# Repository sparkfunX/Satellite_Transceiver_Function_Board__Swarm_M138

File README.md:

SparkX Satellite Transceiver Function Board - Swarm M138
========================================

<p align="center">

</p>

*[SparkX Satellite Transceiver Function Board - Swarm M138 (SPX-20107)](https://www.sparkfun.com/products/20107)*

The [SparkX Satellite Transceiver Function Board - Swarm M138 (SPX-20107)](https://www.sparkfun.com/products/20107) is an adapter which allows you to add Swarm Satellite connectivity
to your [MicroMod](https://www.sparkfun.com/micromod) project. It is designed to be plugged into the [MicroMod Main Board - Single](https://www.sparkfun.com/products/18575)
or [MicroMod Main Board - Double](https://www.sparkfun.com/products/18575). You can then install the Swarm M138 satellite modem and communicate using our dedicated 
[Swarm Satellite Arduino Library](https://github.com/sparkfun/SparkFun_Swarm_Satellite_Arduino_Library).

**Please note: the Swarm M138 modem is not included with the function board.** You will need to purchase the [Satellite Transceiver Breakout - Swarm M138 (SPX-19236)](https://www.sparkfun.com/products/19236)
separately to obtain the modem, antenna and ground plane.

Repository Contents
-------------------

* **[/docs](/docs/)** - Online documentation files
    * [board_files](/docs/board_files/) - Files for the product design
        * [Eagle design files](/docs/board_files/Satellite_Transceiver_Function_Board__Swarm_M138_x04.zip) (.zip)
        * [Schematic](/docs/board_files/Schematic.pdf) (.pdf)
        * [Dimensions](/docs/board_files/Dimensions.png) (.png)
    * [img/hookup_guide/](/docs/img/hookup_guide/) - Images for hookup guide documentation
* **[/Hardware](/Hardware/)** - Eagle design files (.brd, .sch)

Documentation
--------------
* **[Hookup Guide (mkdocs)](https://sparkfunx.github.io/Satellite_Transceiver_Function_Board__Swarm_M138/)** - Hookup guide for the SparkX Satellite Transceiver Function Board - Swarm M138 hosted by GitHub pages.

Product Versions
----------------
* [SPX-20107](https://www.sparkfun.com/products/20107) - Initial SparkX Release

License Information
-------------------

This product is _**open source**_! 

Please review the LICENSE.md file for license information. 

If you have any questions or concerns on licensing, please contact technical support on our [SparkFun forums](https://forum.sparkfun.com/viewforum.php?f=152).

Distributed as-is; no warranty is given.

- Your friends at SparkFun.

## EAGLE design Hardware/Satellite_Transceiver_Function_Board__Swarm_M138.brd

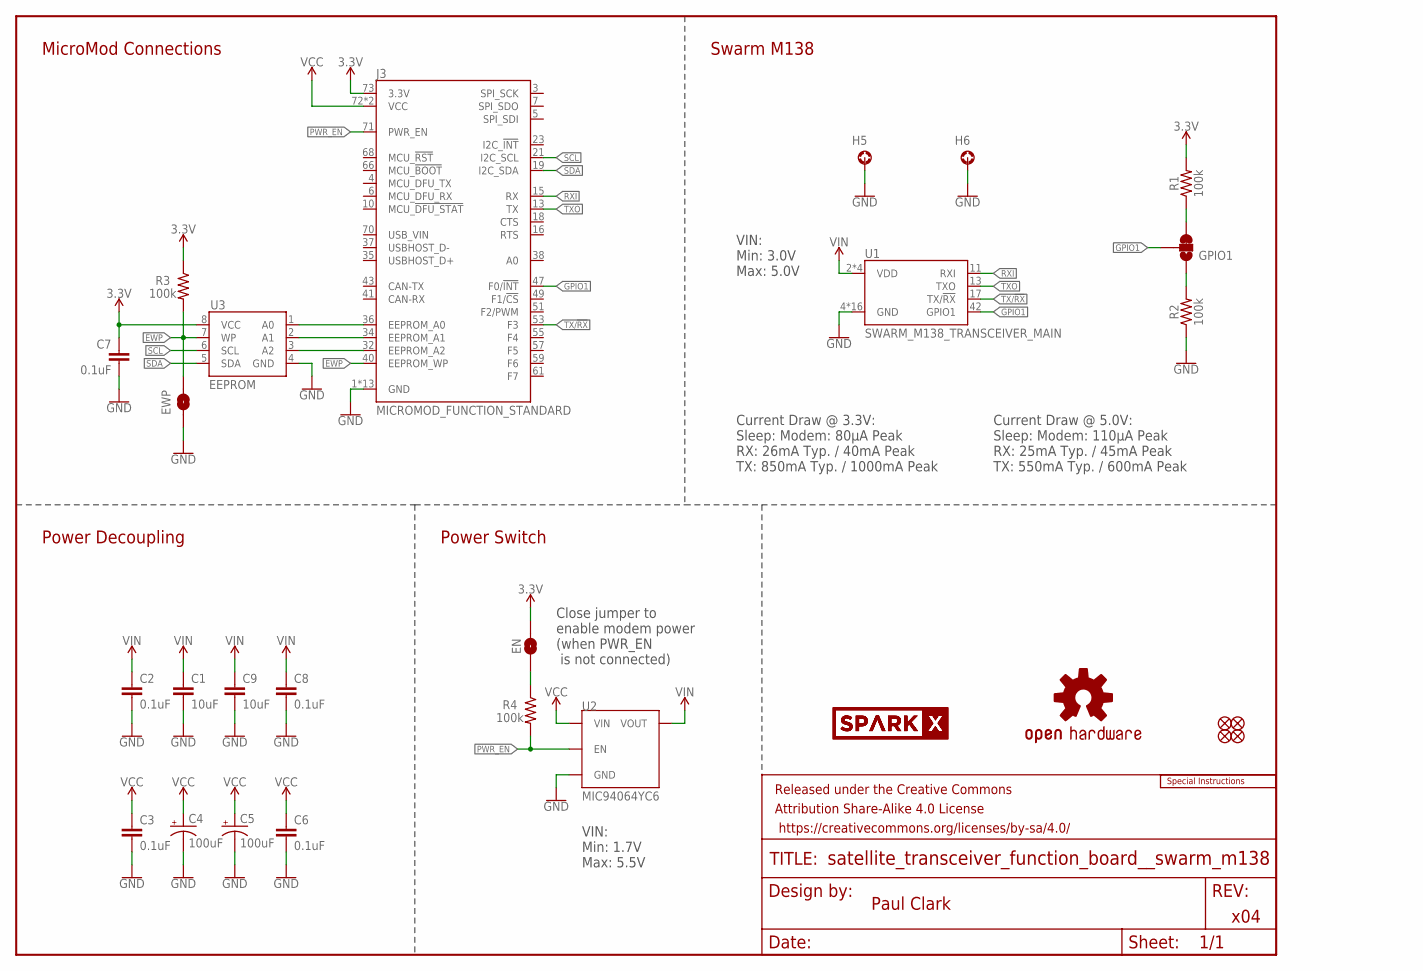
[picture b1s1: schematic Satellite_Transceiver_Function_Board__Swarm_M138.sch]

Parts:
C1, C9: 10uF; 0603
C2, C3, C6, C7, C8: 0.1uF; 0603
C4, C5: 100uF; EIA3528
EN: JUMPER-SMT_2_NO_SILK; SMT-JUMPER_2_NO_SILK
EWP: JUMPER-SMT_2_NO_SILK; SMT-JUMPER_2_NO_SILK
FD1, FD2, FD3, FD4: FIDUCIAL1X2; FIDUCIAL-1X2
FRAME1: FRAME-LETTER; CREATIVE_COMMONS
GPIO1: JUMPER-SMT_3_1-NC_TRACE_SILK; SMT-JUMPER_3_1-NC_TRACE_SILK
H5, H6: STAND-OFF-REFLOW-M2.5_1.5MM_TALL; STAND-OFF-REFLOW-M2.5
J3: MICROMOD_FUNCTION_STANDARD; M.2-CARD-E-22_FUNCTION_STANDARD
LOGO1: SPECIAL_INSTRUCTIONS-ORDERING; ORDERING_INSTRUCTIONS
LOGO2: OSHW-LOGOS; OSHW-LOGO-S
R1, R2, R3, R4: 100k; 0603
U1: SWARM_M138_TRANSCEIVER_MAIN; M.2-SWARM-M138-A
U2: MIC94064YC6; SC-70-6
U3: EEPROM; SO08
U$1, U$2: SPARKX-LOGO5; SPARKX-LARGE

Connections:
3.3V: C7.1, EN.2, J3.73 (3.3V), R1.2, R3.1, U3.8 (VCC)
A0: J3.36 (EEPROM_A0), U3.1 (A0)
A1: J3.34 (EEPROM_A1), U3.2 (A1)
A2: J3.32 (EEPROM_A2), U3.3 (A2)
EWP: EWP.2, J3.40 (EEPROM_WP), R3.2, U3.7 (WP)
GND: C1.2, C2.2, C3.2, C4.C (-), C5.C (-), C6.2, C7.2, C8.2, C9.2, EWP.1, H5.1, H6.1, J3.1 (GND), J3.2 (GND), J3.8 (GND), J3.33 (GND), J3.39 (GND), J3.45 (GND), J3.75 (GND), J3.GND1 (GND), J3.GND2 (GND), J3.GND3 (GND), J3.GND4 (GND), J3.GND5 (GND), J3.GND6 (GND), R2.1, U1.4 (GND), U1.9 (GND), U1.15 (GND), U1.18 (GND), U1.21 (GND), U1.26 (GND), U1.27 (GND), U1.29 (GND), U1.34 (GND), U1.35 (GND), U1.37 (GND), U1.40 (GND), U1.43 (GND), U1.50 (GND), U1.A1 (GND), U1.A2 (GND), U2.2 (GND), U2.5 (GND), U3.4 (GND)
GPIO1: GPIO1.2, J3.47 (F0/!INT!), U1.42 (GPIO1)
unnamed: EN.1, R4.1
unnamed: GPIO1.3, R1.1
unnamed: GPIO1.1, R2.2
PWR_EN: J3.71 (PWR_EN), R4.2, U2.3 (EN)
RXI: J3.15 (RX), U1.11 (RXI)
SCL: J3.21 (I2C_SCL), U3.6 (SCL)
SDA: J3.19 (I2C_SDA), U3.5 (SDA)
TX/!RX!: J3.53 (F3), U1.17 (TX/!RX!)
TXO: J3.13 (TX), U1.13 (TXO)
VCC: C3.1, C4.A (+), C5.A (+), C6.1, J3.72 (VCC), J3.74 (VCC), U2.4 (VIN)
VIN: C1.1, C2.1, C8.1, C9.1, U1.2 (VDD), U1.39 (VDD), U1.41 (VDD), U1.52 (VDD), U2.1 (VOUT)

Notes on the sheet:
x04
Paul Clark
Power Switch
Power Decoupling
Swarm M138
VIN: Min: 3.0V Max: 5.0V
Current Draw @ 3.3V: Sleep: Modem: 80µA Peak RX: 26mA Typ. / 40mA Peak TX: 850mA Typ. / 1000mA Peak
Current Draw @ 5.0V: Sleep: Modem: 110µA Peak RX: 25mA Typ. / 45mA Peak TX: 550mA Typ. / 600mA Peak
MicroMod Connections
VIN: Min: 1.7V Max: 5.5V
Close jumper to enable modem power (when PWR_EN is not connected)

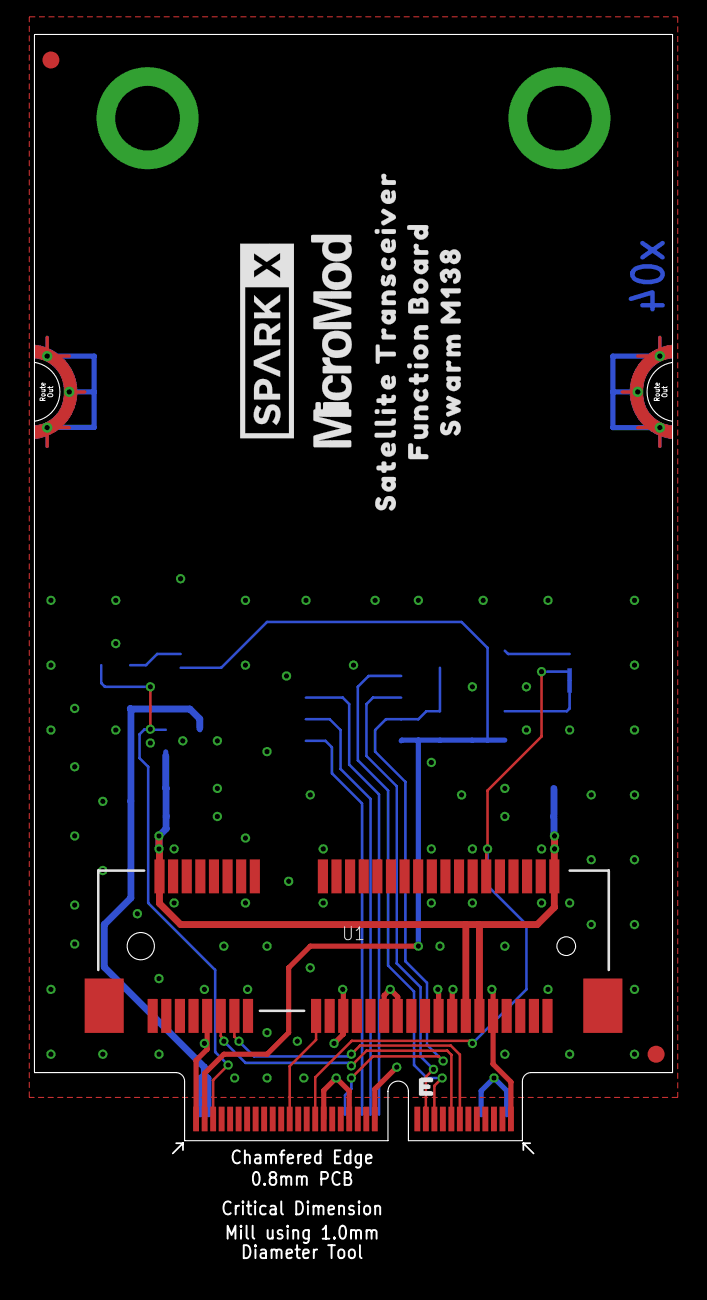
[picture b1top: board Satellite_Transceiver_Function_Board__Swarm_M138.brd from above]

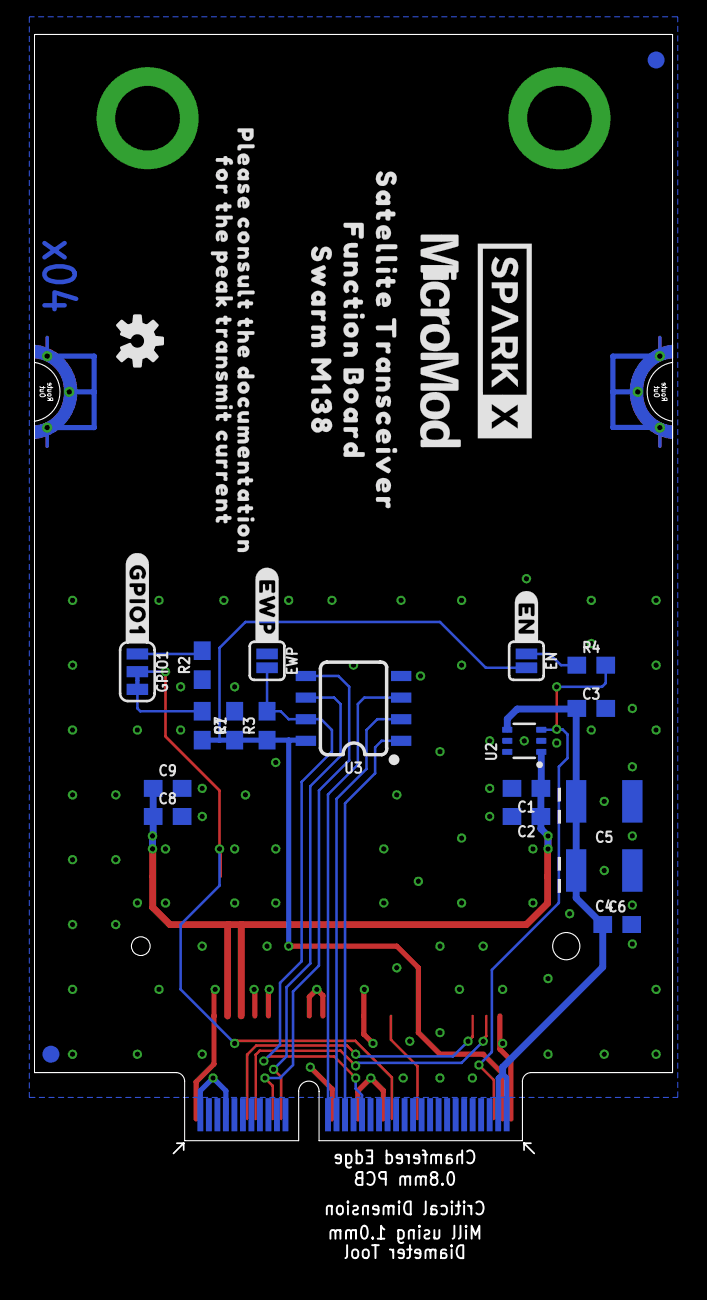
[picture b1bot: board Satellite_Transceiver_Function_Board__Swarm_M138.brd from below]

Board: 2 copper layers, 37.4 x 72.3 mm, 44 parts (31 on the bottom side), 18 nets.

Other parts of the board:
U$3, U$7: FUNCTION_BOARD0
U$4, U$5: SATELLITE_TRANSCEIVER0
U$6: PLEASE_CONSULT_THE_DOCUMENTATION0
U$8: #EWP#0
U$9, U$10: MICROMOD_LOGO_.5
U$11: #EN#0
U$19: #GPIO1#0
U$31: FOR_THE_PEAK_TRANSMIT_CURRENT1
U$40, U$41: SWARM_M1381

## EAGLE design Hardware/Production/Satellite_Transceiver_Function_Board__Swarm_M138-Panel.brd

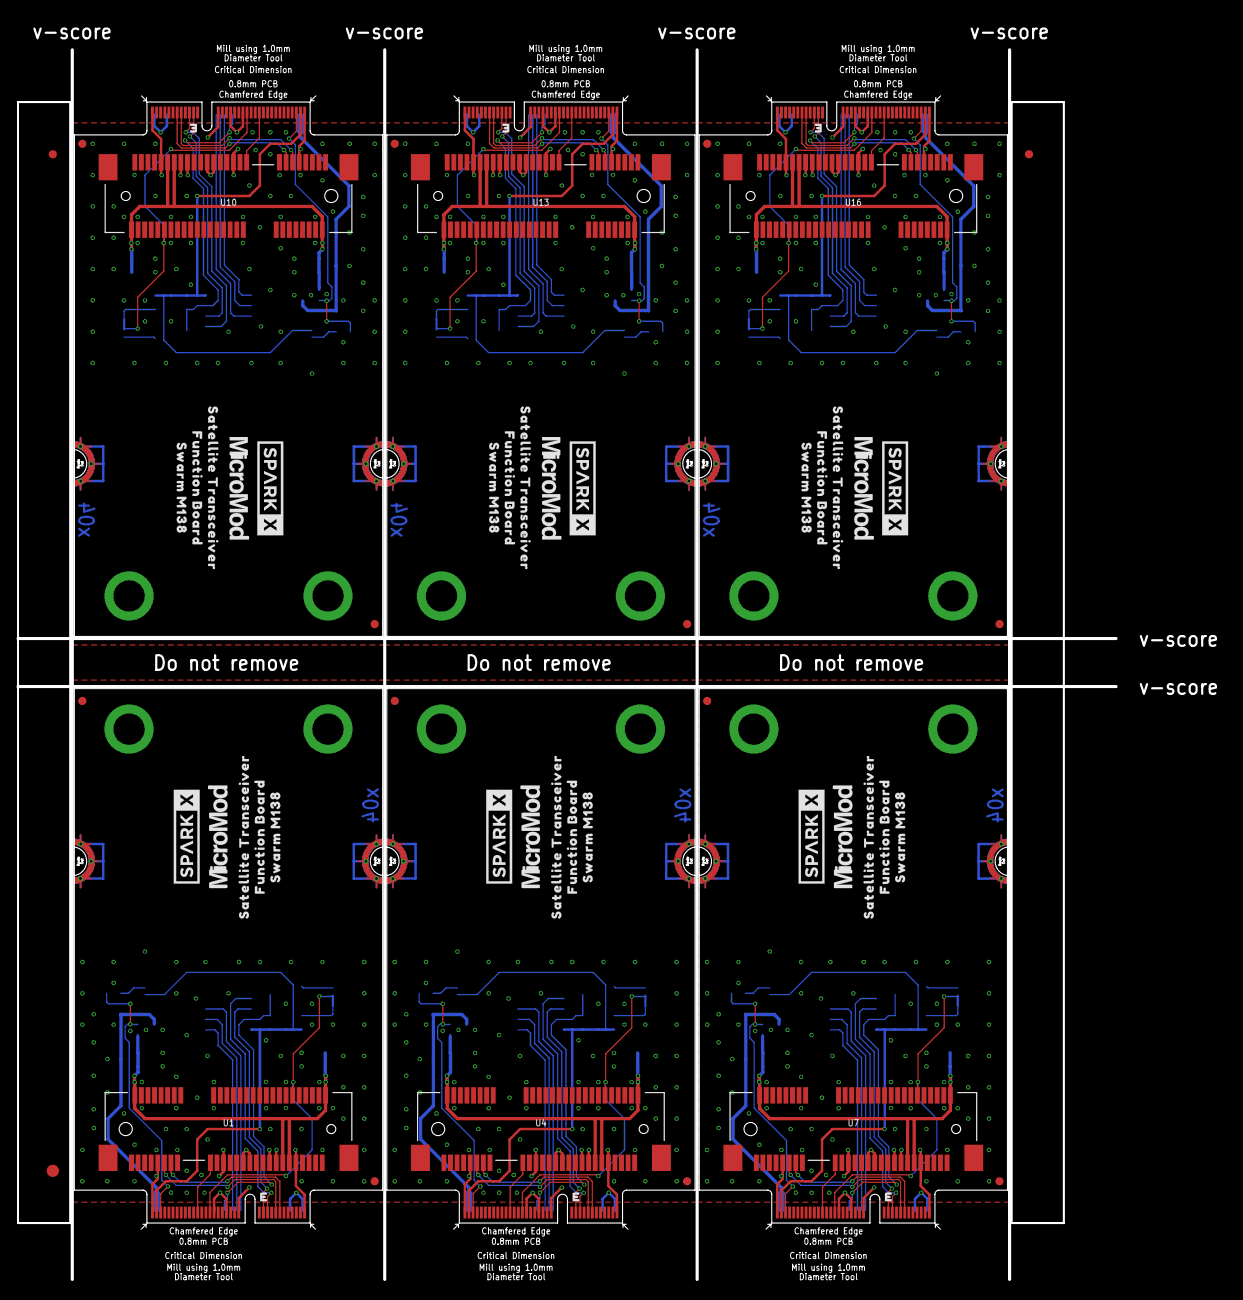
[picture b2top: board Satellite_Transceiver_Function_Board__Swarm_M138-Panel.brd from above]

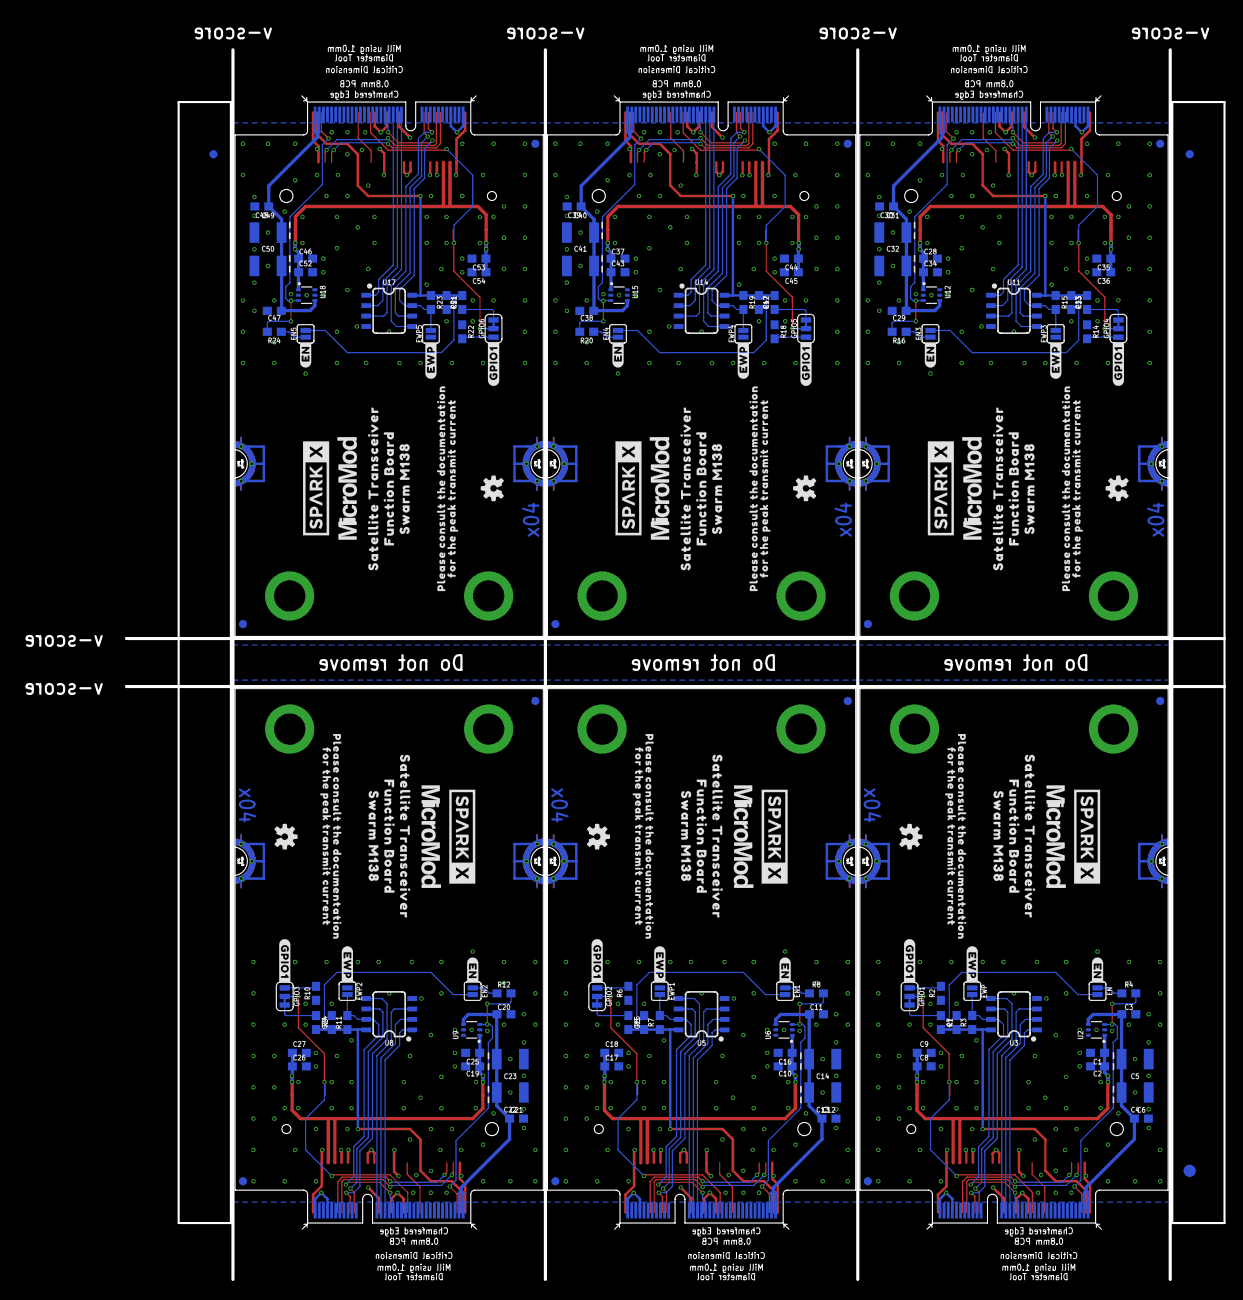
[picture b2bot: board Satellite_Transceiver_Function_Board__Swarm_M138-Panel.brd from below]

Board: 2 copper layers, 146.7 x 153.7 mm, 258 parts (189 on the bottom side), 108 nets.

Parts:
C1, C9, C16, C18, C25, C27, C34, C36, C43, C45, C52, C54: 10uF; 0603
C2, C3, C6, C7, C8, C10, C11, C12, C15, C17, C19, C20, C21, C24, C26, C28, C29, C30, C33, C35, C37, C38, C39, C42, C44, C46, C47, C48, C51, C53: 0.1uF; 0603
C4, C5, C13, C14, C22, C23, C31, C32, C40, C41, C49, C50: 100uF; EIA3528
E$1, E$2, E$3, E$4: FIDUCIAL-1X2
E$5, E$6: FIDUCIAL-1.5X3
EN, EN1, EN2, EN3, EN4, EN5: JUMPER-SMT_2_NO_SILK; SMT-JUMPER_2_NO_SILK
EWP, EWP1, EWP2, EWP3, EWP4, EWP5: JUMPER-SMT_2_NO_SILK; SMT-JUMPER_2_NO_SILK
FD1, FD2, FD3, FD4, FD5, FD6, FD7, FD8, FD9, FD10, FD11, FD12, FD13, FD14, FD15, FD16, FD17, FD18, FD19, FD20, FD21, FD22, FD23, FD24: FIDUCIAL1X2; FIDUCIAL-1X2
GPIO1, GPIO2, GPIO3, GPIO4, GPIO5, GPIO6: JUMPER-SMT_3_1-NC_TRACE_SILK; SMT-JUMPER_3_1-NC_TRACE_SILK
H1, H2, H3, H4, H5, H6, H7, H8, H9, H10, H11, H12: STAND-OFF-REFLOW-M2.5_1.5MM_TALL; STAND-OFF-REFLOW-M2.5
J1, J2, J3, J4, J5, J6: MICROMOD_FUNCTION_STANDARD; M.2-CARD-E-22_FUNCTION_STANDARD
LOGO1, LOGO2, LOGO3, LOGO4, LOGO5, LOGO6: OSHW-LOGOS; OSHW-LOGO-S
R1, R2, R3, R4, R5, R6, R7, R8, R9, R10, R11, R12, R13, R14, R15, R16, R17, R18, R19, R20, R21, R22, R23, R24: 100k; 0603
U1, U4, U7, U10, U13, U16: SWARM_M138_TRANSCEIVER_MAIN; M.2-SWARM-M138-A
U2, U6, U9, U12, U15, U18: MIC94064YC6; SC-70-6
U3, U5, U8, U11, U14, U17: EEPROM; SO08
U$1, U$2, U$12, U$13, U$28, U$29, U$46, U$47, U$61, U$62, U$76, U$77: SPARKX-LOGO5; SPARKX-LARGE
U$3, U$7, U$20, U$23, U$36, U$39, U$53, U$56, U$68, U$71, U$83, U$86: FUNCTION_BOARD0
U$4, U$5, U$21, U$22, U$37, U$38, U$54, U$55, U$69, U$70, U$84, U$85: SATELLITE_TRANSCEIVER0
U$6, U$17, U$34, U$51, U$66, U$81: PLEASE_CONSULT_THE_DOCUMENTATION0
U$8, U$24, U$42, U$57, U$72, U$87: #EWP#0
U$9, U$10, U$25, U$26, U$43, U$44, U$58, U$59, U$73, U$74, U$88, U$89: MICROMOD_LOGO_.5
U$11, U$27, U$45, U$60, U$75, U$90: #EN#0
U$14, U$19, U$30, U$48, U$63, U$78: #GPIO1#0
U$15, U$16, U$32, U$33, U$40, U$41, U$49, U$50, U$64, U$65, U$79, U$80: SWARM_M1381
U$18, U$31, U$35, U$52, U$67, U$82: FOR_THE_PEAK_TRANSMIT_CURRENT1

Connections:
3.3V: C7.1, EN.2, J3.73, R1.2, R3.1, U3.8
3.3V1: C15.1, EN1.2, J1.73, R5.2, R7.1, U5.8
3.3V2: C24.1, EN2.2, J2.73, R9.2, R11.1, U8.8
3.3V3: C33.1, EN3.2, J4.73, R13.2, R15.1, U11.8
3.3V4: C42.1, EN4.2, J5.73, R17.2, R19.1, U14.8
3.3V5: C51.1, EN5.2, J6.73, R21.2, R23.1, U17.8
A0: J3.36, U3.1
A1: J3.34, U3.2
A2: J3.32, U3.3
A3: J1.36, U5.1
A4: J1.32, U5.3
A5: J1.34, U5.2
A6: J2.36, U8.1
A7: J2.32, U8.3
A8: J2.34, U8.2
A9: J4.36, U11.1
A10: J4.32, U11.3
A11: J4.34, U11.2
A12: J5.36, U14.1
A13: J5.32, U14.3
A14: J5.34, U14.2
A15: J6.36, U17.1
A16: J6.32, U17.3
A17: J6.34, U17.2
EWP: EWP.2, J3.40, R3.2, U3.7
EWP1: EWP1.2, J1.40, R7.2, U5.7
EWP2: EWP2.2, J2.40, R11.2, U8.7
EWP3: EWP3.2, J4.40, R15.2, U11.7
EWP4: EWP4.2, J5.40, R19.2, U14.7
EWP5: EWP5.2, J6.40, R23.2, U17.7
GND: C1.2, C2.2, C3.2, C4.C, C5.C, C6.2, C7.2, C8.2, C9.2, EWP.1, H5.1, H6.1, J3.1, J3.2, J3.8, J3.33, J3.39, J3.45, J3.75, J3.GND1, J3.GND2, J3.GND3, J3.GND4, J3.GND5, J3.GND6, R2.1, U1.4, U1.9, U1.15, U1.18, U1.21, U1.26, U1.27, U1.29, U1.34, U1.35, U1.37, U1.40, U1.43, U1.50, U1.A1, U1.A2, U2.2, U2.5, U3.4
GND1: C10.2, C11.2, C12.2, C13.C, C14.C, C15.2, C16.2, C17.2, C18.2, EWP1.1, H1.1, H2.1, J1.1, J1.2, J1.8, J1.33, J1.39, J1.45, J1.75, J1.GND1, J1.GND2, J1.GND3, J1.GND4, J1.GND5, J1.GND6, R6.1, U4.4, U4.9, U4.15, U4.18, U4.21, U4.26, U4.27, U4.29, U4.34, U4.35, U4.37, U4.40, U4.43, U4.50, U4.A1, U4.A2, U5.4, U6.2, U6.5
GND2: C19.2, C20.2, C21.2, C22.C, C23.C, C24.2, C25.2, C26.2, C27.2, EWP2.1, H3.1, H4.1, J2.1, J2.2, J2.8, J2.33, J2.39, J2.45, J2.75, J2.GND1, J2.GND2, J2.GND3, J2.GND4, J2.GND5, J2.GND6, R10.1, U7.4, U7.9, U7.15, U7.18, U7.21, U7.26, U7.27, U7.29, U7.34, U7.35, U7.37, U7.40, U7.43, U7.50, U7.A1, U7.A2, U8.4, U9.2, U9.5
GND3: C28.2, C29.2, C30.2, C31.C, C32.C, C33.2, C34.2, C35.2, C36.2, EWP3.1, H7.1, H8.1, J4.1, J4.2, J4.8, J4.33, J4.39, J4.45, J4.75, J4.GND1, J4.GND2, J4.GND3, J4.GND4, J4.GND5, J4.GND6, R14.1, U10.4, U10.9, U10.15, U10.18, U10.21, U10.26, U10.27, U10.29, U10.34, U10.35, U10.37, U10.40, U10.43, U10.50, U10.A1, U10.A2, U11.4, U12.2, U12.5
GND4: C37.2, C38.2, C39.2, C40.C, C41.C, C42.2, C43.2, C44.2, C45.2, EWP4.1, H9.1, H10.1, J5.1, J5.2, J5.8, J5.33, J5.39, J5.45, J5.75, J5.GND1, J5.GND2, J5.GND3, J5.GND4, J5.GND5, J5.GND6, R18.1, U13.4, U13.9, U13.15, U13.18, U13.21, U13.26, U13.27, U13.29, U13.34, U13.35, U13.37, U13.40, U13.43, U13.50, U13.A1, U13.A2, U14.4, U15.2, U15.5
GND5: C46.2, C47.2, C48.2, C49.C, C50.C, C51.2, C52.2, C53.2, C54.2, EWP5.1, H11.1, H12.1, J6.1, J6.2, J6.8, J6.33, J6.39, J6.45, J6.75, J6.GND1, J6.GND2, J6.GND3, J6.GND4, J6.GND5, J6.GND6, R22.1, U16.4, U16.9, U16.15, U16.18, U16.21, U16.26, U16.27, U16.29, U16.34, U16.35, U16.37, U16.40, U16.43, U16.50, U16.A1, U16.A2, U17.4, U18.2, U18.5
GPIO1: GPIO1.2, J3.47, U1.42
GPIO2: GPIO2.2, J1.47, U4.42
GPIO3: GPIO3.2, J2.47, U7.42
GPIO4: GPIO4.2, J4.47, U10.42
GPIO5: GPIO5.2, J5.47, U13.42
GPIO6: GPIO6.2, J6.47, U16.42
unnamed: EN.1, R4.1
unnamed: GPIO2.3, R5.1
unnamed: GPIO2.1, R6.2
unnamed: EN1.1, R8.1
unnamed: GPIO3.3, R9.1
unnamed: GPIO3.1, R10.2
unnamed: EN2.1, R12.1
unnamed: GPIO4.3, R13.1
unnamed: GPIO4.1, R14.2
unnamed: EN3.1, R16.1
unnamed: GPIO5.3, R17.1
unnamed: GPIO5.1, R18.2
unnamed: EN4.1, R20.1
unnamed: GPIO1.3, R1.1
unnamed: GPIO6.3, R21.1
unnamed: GPIO1.1, R2.2
unnamed: GPIO6.1, R22.2
unnamed: EN5.1, R24.1
PWR_EN: J3.71, R4.2, U2.3
PWR_EN1: J1.71, R8.2, U6.3
PWR_EN2: J2.71, R12.2, U9.3
PWR_EN3: J4.71, R16.2, U12.3
PWR_EN4: J5.71, R20.2, U15.3
PWR_EN5: J6.71, R24.2, U18.3
RXI: J3.15, U1.11
RXI1: J1.15, U4.11
RXI2: J2.15, U7.11
RXI3: J4.15, U10.11
RXI4: J5.15, U13.11
RXI5: J6.15, U16.11
SCL: J3.21, U3.6
SCL1: J1.21, U5.6
SCL2: J2.21, U8.6
SCL3: J4.21, U11.6
SCL4: J5.21, U14.6
SCL5: J6.21, U17.6
SDA: J3.19, U3.5
SDA1: J1.19, U5.5
SDA2: J2.19, U8.5
SDA3: J4.19, U11.5
SDA4: J5.19, U14.5
SDA5: J6.19, U17.5
TX/!RX!: J3.53, U1.17
TX/!RX!1: J1.53, U4.17
TX/!RX!2: J2.53, U7.17
TX/!RX!3: J4.53, U10.17
TX/!RX!4: J5.53, U13.17
TX/!RX!5: J6.53, U16.17
TXO: J3.13, U1.13
TXO1: J1.13, U4.13
TXO2: J2.13, U7.13
TXO3: J4.13, U10.13
TXO4: J5.13, U13.13
TXO5: J6.13, U16.13
VCC: C3.1, C4.A, C5.A, C6.1, J3.72, J3.74, U2.4
VCC1: C11.1, C12.1, C13.A, C14.A, J1.72, J1.74, U6.4
VCC2: C20.1, C21.1, C22.A, C23.A, J2.72, J2.74, U9.4
VCC3: C29.1, C30.1, C31.A, C32.A, J4.72, J4.74, U12.4
VCC4: C38.1, C39.1, C40.A, C41.A, J5.72, J5.74, U15.4
VCC5: C47.1, C48.1, C49.A, C50.A, J6.72, J6.74, U18.4
VIN: C1.1, C2.1, C8.1, C9.1, U1.2, U1.39, U1.41, U1.52, U2.1
VIN1: C10.1, C16.1, C17.1, C18.1, U4.2, U4.39, U4.41, U4.52, U6.1
VIN2: C19.1, C25.1, C26.1, C27.1, U7.2, U7.39, U7.41, U7.52, U9.1
VIN3: C28.1, C34.1, C35.1, C36.1, U10.2, U10.39, U10.41, U10.52, U12.1
VIN4: C37.1, C43.1, C44.1, C45.1, U13.2, U13.39, U13.41, U13.52, U15.1
VIN5: C46.1, C52.1, C53.1, C54.1, U16.2, U16.39, U16.41, U16.52, U18.1

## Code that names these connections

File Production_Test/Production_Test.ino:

/*

  Production Test Code for the:
  SparkX Satellite Transceiver Function Board - Swarm M138 (SPX-20107)
  https://www.sparkfun.com/products/20107
  https://github.com/sparkfunX/Satellite_Transceiver_Function_Board__Swarm_M138

  Hardware Required:

  * A Swarm M138 modem - taken from: Satellite Transceiver Breakout - Swarm M138: https://www.sparkfun.com/products/19236
  * SparkFun MicroMod Main Board - Double: https://www.sparkfun.com/products/18576
  * SparkFun MicroMod ESP32 Processor: https://www.sparkfun.com/products/16781
  * USB Cable

  Setup:

  * Install the ESP32 Processor Board in the Main Board - Double
  * Set the ALT_PWR_EN0 jumper to G5<->PWR_EN0
  * Select the ESP32 Arduino \ SparkFun ESP32 MicroMod processor
  * Connect the Main Board - Double to your computer via USB
  * Upload this sketch onto the ESP32
  * Open the Serial Monitor at 115200 baud to see the output
  
  Test Procedure:

  * Insert the Swarm M138 modem into the Function Board. No need to screw it down
  * Insert the Function Board into the Main Board Slot 0. No need to screw it down. Just hold both boards down with your finger
  * This code:
    * Powers up the M138 modem via the PWR_EN pin
    * Begins serial communication with the modem
    * Checks the firmware version
    * Checks that the GPIO1 pin can be pulled high and low
    * Tells the modem to powerOff (to avoid weirdness)
    * Waits until the modem is disconnected
 
 */

#include <SparkFun_Swarm_Satellite_Arduino_Library.h> //Click here to get the library:  http://librarymanager/All#SparkFun_Swarm_Satellite

SWARM_M138 mySwarm;
#define swarmSerial Serial1 // Use Serial1 to communicate with the modem

// Swarm Satellite Transceiver MicroMod Function Board:
// Uncomment and adapt a line to match your Main Board and Processor configuration:
#define swarmPowerEnablePin G5 // MicroMod Main Board Double (DEV-18576) : Slot 0 with the ALT_PWR_EN0 set to G5<->PWR_EN0
#define swarmGPIO1pin D0 // MicroMod Main Board Double (DEV-18576) : Slot 0

void setup()
{
  //mySwarm.enableDebugging(); // Uncomment this line to enable debug messages on Serial

  delay(2000);
  
  Serial.begin(115200);
  while (!Serial)
    ; // Wait for the user to open the Serial console
  Serial.println(F("Swarm Satellite Function Board - Test Procedure"));
  Serial.println();

  pinMode(LED_BUILTIN, OUTPUT);
  digitalWrite(LED_BUILTIN, LOW); // Turn the LED off

  pinMode(swarmGPIO1pin, INPUT_PULLUP); // Use the pull-up to indicate when the board has been removed

  pinMode(swarmPowerEnablePin, OUTPUT);
  digitalWrite(swarmPowerEnablePin, HIGH); // Enable the high-side power switch
}

void loop()
{
  digitalWrite(LED_BUILTIN, LOW); // Turn the LED off
  
  bool modemBegun = mySwarm.begin(swarmSerial); // Begin communication with the modem

  int beginTries = 0;
  
  while (!modemBegun) // If the begin failed, keep trying to begin communication with the modem
  {
    if (beginTries < 10)
      Serial.println(F("Could not communicate with the modem. It may still be booting..."));
    else
      Serial.println(F("Could not communicate with the modem. Check the M.2 gold finger alignment..."));
    delay(1000);
    modemBegun = mySwarm.begin(swarmSerial);
    beginTries++;
  }

  char firmwareVersion[SWARM_M138_MEM_ALLOC_FV]; // Create storage for the configuration settings

  if (mySwarm.getFirmwareVersion(firmwareVersion) == SWARM_M138_SUCCESS) // Get the firmware version
  {
    Serial.print(F("Modem found! The firmware version is: "));
    Serial.println(firmwareVersion);

    delay(100);
    
    bool keepGoing = (mySwarm.setGPIO1Mode(SWARM_M138_GPIO1_OUTPUT_HIGH) == SWARM_M138_SUCCESS); // Set GPIO1 high

    if (keepGoing)
    {
      delay(100);

      keepGoing = (digitalRead(swarmGPIO1pin) == HIGH); // Check GPIO1 is high

      if (keepGoing)
      {
        delay(100);

        keepGoing = (mySwarm.setGPIO1Mode(SWARM_M138_GPIO1_OUTPUT_LOW) == SWARM_M138_SUCCESS); // Set GPIO1 low

        if (keepGoing)
        {
          delay(100);

          keepGoing = (digitalRead(swarmGPIO1pin) == LOW); // Check GPIO1 is low

          if (keepGoing)
          {
            Serial.println(F("TEST PASSED!"));
            digitalWrite(LED_BUILTIN, HIGH); // Turn the LED on

            delay(100);

            Serial.print(F("Telling the modem to power off...: "));

            keepGoing = (mySwarm.powerOff() == SWARM_M138_SUCCESS); // Modem Power Off

            if (keepGoing)
              Serial.print(F("powerOff was successful! Remove this board and insert the next one"));
            else
              Serial.print(F("powerOff FAILED! Remove this board and re-insert it for a re-test"));

            while (digitalRead(swarmGPIO1pin) == LOW)
            {
              delay(1000);
              Serial.print(F("."));
            }

            Serial.println();
            Serial.println(F("Ready for the next board..."));
          }
          else
          {
            Serial.println(F("TEST FAILED! GPIO1 is high when it should be low. (Possible dry joint on GPIO1?)"));
            delay(1000);
          }
        }
        else
        {
          Serial.println(F("TEST FAILED! Could not set the GPIO1 pin mode to SWARM_M138_GPIO1_OUTPUT_LOW. (Possible TXI/RXO pin error?)"));                
          delay(1000);
        }
      }
      else
      {
        Serial.println(F("TEST FAILED! GPIO1 is low when it should be high. (Possible dry joint on GPIO1?)"));          
        delay(1000);
      }
    }
    else
    {
      Serial.println(F("TEST FAILED! Could not set the GPIO1 pin mode to SWARM_M138_GPIO1_OUTPUT_HIGH. (Possible TXO/RXI pin error?)"));    
      delay(1000);
    }
  }
  else
  {
    Serial.println(F("TEST FAILED! Could not read the firmware version. (Possible TXO/RXI pin error?)"));
    delay(1000);
  }
}

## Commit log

2022-05-23 x01 PCB
2022-05-26 x03_PCB
2022-07-22 x04 PCB
2022-08-22 Docs updates
2022-09-01 mkdocs yaml update - add workflow_dispatch
2023-03-04 Deployed 0beea73 with MkDocs version: 1.4.2

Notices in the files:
README.md:
License: CC BY-SA 4.0
parts and their libraries:
SparkFun-Aesthetics: Licensing: Creative Commons ShareAlike 4.0 International - https://creativecommons.org/licenses/by-sa/4.0
SparkFun-Aesthetics: Released under the Creative Commons Attribution Share-Alike 4.0 License
SparkFun-Aesthetics: https://creativecommons.org/licenses/by-sa/4.0
